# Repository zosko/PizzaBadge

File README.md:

# Pizza Badge

8 Slices pizza badge presented with LEDs. Slices will light when they receive response from server how many points you have.

## Scheme

## Boards
Board|PCB Empty|PCB filled
---------|---------|---------
||

## 3D Case
With PCB|Case Empty
---------|---------
|

## PCB Design

For PCB design i will use services from SeeedFusion. 

Seeed Fusion PCB Assembly Service offers one-stop prototyping for PCB manufacture, PCB assembly and as a result they produce superior quality PCBs and Fast Turnkey PCBA from 7 working days. When you prototype with Seeed Fusion, they can definitely provide Free DFA and Free functional tests for you! 

Check out their website to know about their manufacturing capabilities and service.
https://www.seeedstudio.com/prototype-pcb-assembly.html 

## Seeed Fusion PCBs
Empty PCB|Finished PCB
--------|--------
|

## Demo

## Reasons to choose Seeed Studio
- They provide PCB services at extremely low pricing and with excellent quality.
- Their offer is structured in such a way that everyone may have these boards at a reasonable price.
- They have a highly knowledgeable crew that leads their clients to avail deals and guides them about the costs and rates of different services.
- A four-layer board with a comparable feature costs $5 for 10 pieces and is made in four days.
- SMT stencil with size (10cm x 13cm) is available for $8.00 per piece.

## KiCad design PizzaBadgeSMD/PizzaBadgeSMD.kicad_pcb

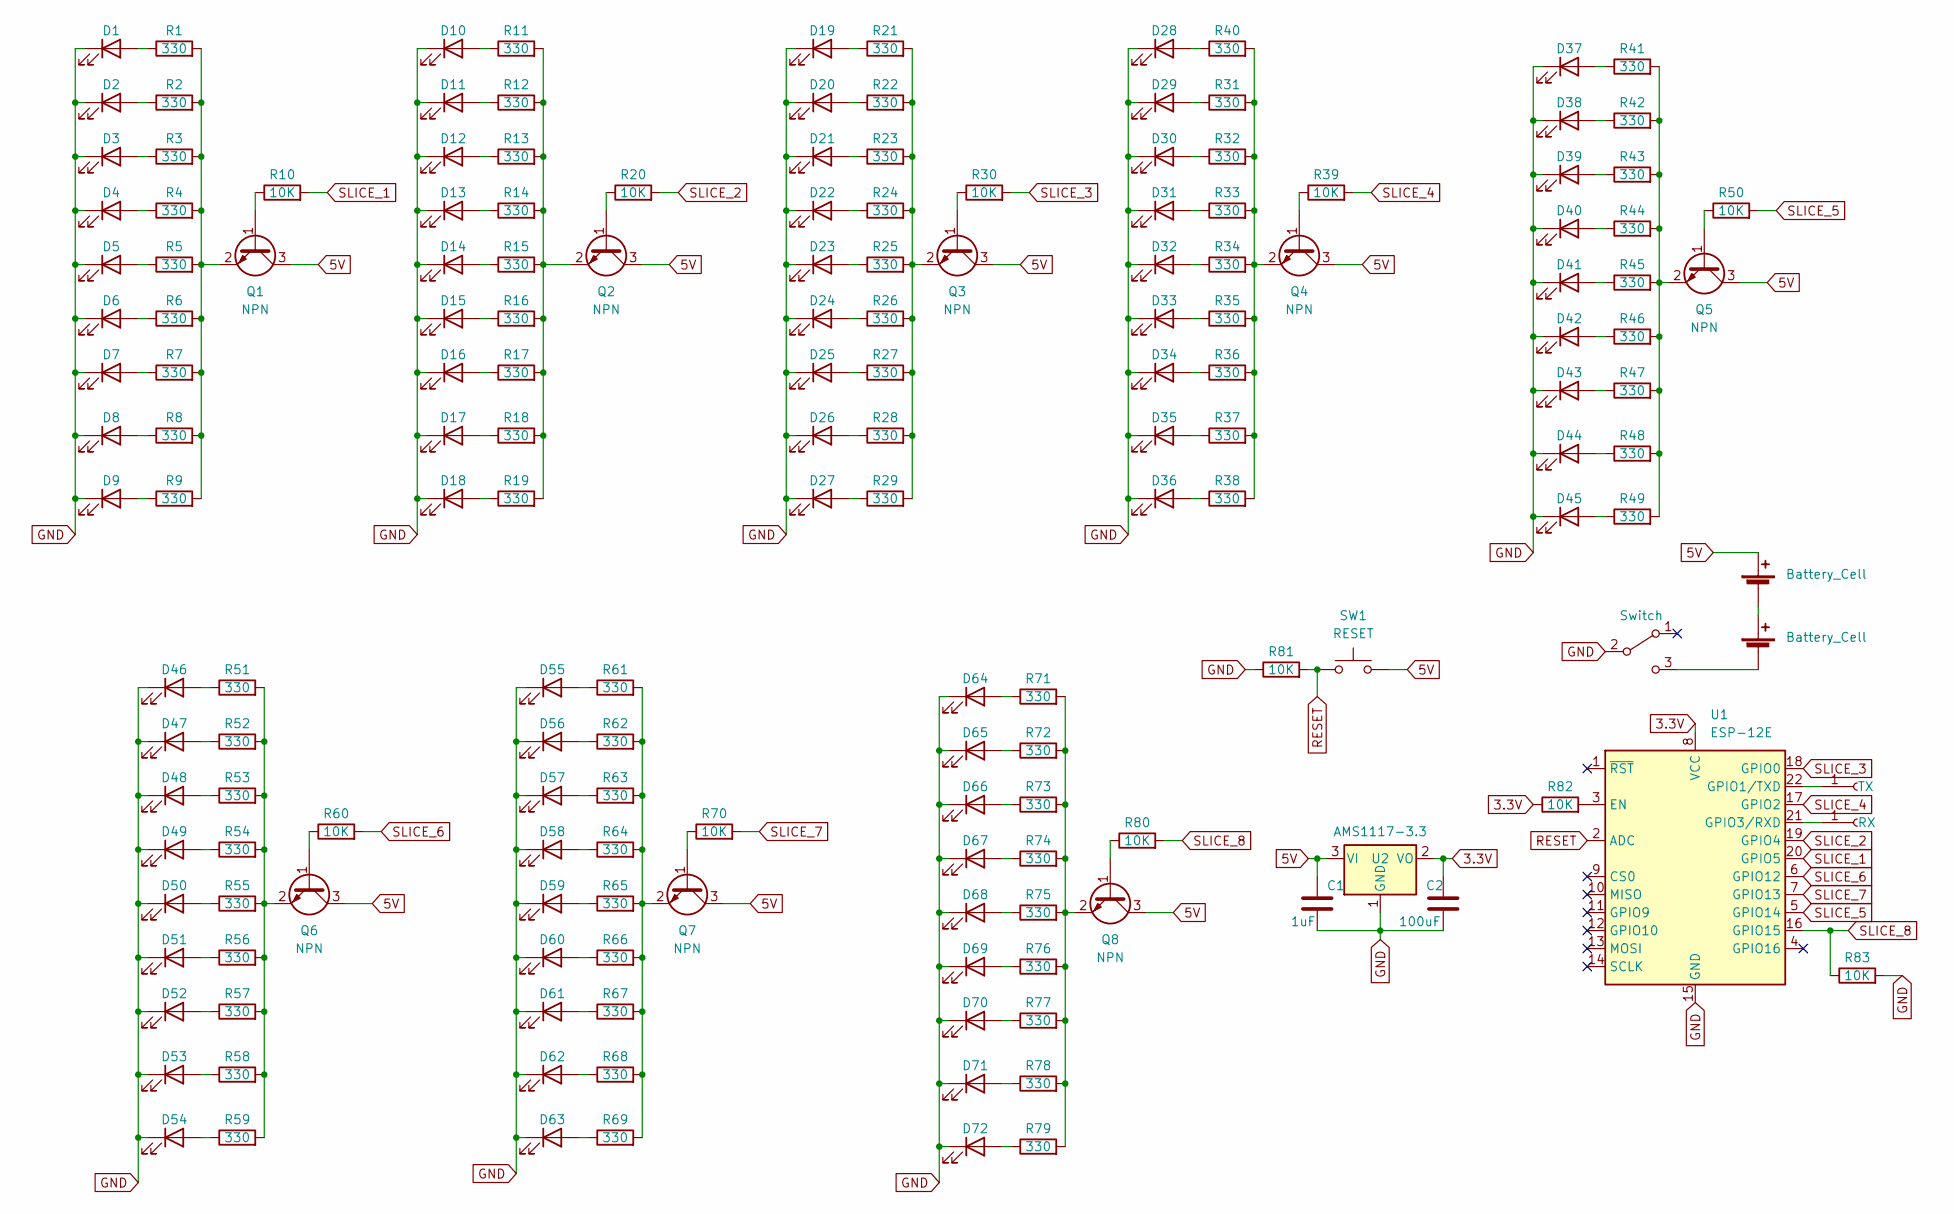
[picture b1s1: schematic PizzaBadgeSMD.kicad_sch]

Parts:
BT1, BT2: Battery_Cell; BatteryHolder_Keystone_3000_1x12mm
C1: 1uF; C_0805_2012Metric
C2: 100uF; C_0805_2012Metric
D1, D2, D3, D4, D5, D6, D7, D8, D9, D10, D11, D12, D13, D14, D15, D16, D17, D18, D19, D20, D21, D22, D23, D24, D25, D26, D27, D28, D29, D30, D31, D32, D33, D34, D35, D36, D37, D38, D39, D40, D41, D42, D43, D44, D45, D46, D47, D48, D49, D50, D51, D52, D53, D54, D55, D56, D57, D58, D59, D60, D61, D62, D63, D64, D65, D66, D67, D68, D69, D70, D71, D72: LED; LED_0805_2012Metric
J1: TX; TestPoint_Pad_2.0x2.0mm
J2: RX; TestPoint_Pad_2.0x2.0mm
Q1, Q2, Q3, Q4, Q5, Q6, Q7, Q8: NPN; SOT-23
R1, R2, R3, R4, R5, R6, R7, R8, R9, R11, R12, R13, R14, R15, R16, R17, R18, R19, R21, R22, R23, R24, R25, R26, R27, R28, R29, R31, R32, R33, R34, R35, R36, R37, R38, R40, R41, R42, R43, R44, R45, R46, R47, R48, R49, R51, R52, R53, R54, R55, R56, R57, R58, R59, R61, R62, R63, R64, R65, R66, R67, R68, R69, R71, R72, R73, R74, R75, R76, R77, R78, R79: 330; R_0805_2012Metric
R10, R20, R30, R39, R50, R60, R70, R80, R81, R82, R83: 10K; R_0805_2012Metric
SW1: RESET; SW_SPST_CK_RS282G05A3
SW2: Switch; SW_SPDT_PCM12
U1: ESP-12E
U2: AMS1117-3.3; SOT-223-3_TabPin2

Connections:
3.3V: C2.1, R82.1, U1.8 (VCC), U2.2 (VO)
5V: BT1.1 (+), C1.1, Q1.3 (C), Q2.3 (C), Q3.3 (C), Q4.3 (C), Q5.3 (C), Q6.3 (C), Q7.3 (C), Q8.3 (C), SW1.2, U2.3 (VI)
GND: C1.2, C2.2, D1.1 (K), D2.1 (K), D3.1 (K), D4.1 (K), D5.1 (K), D6.1 (K), D7.1 (K), D8.1 (K), D9.1 (K), D10.1 (K), D11.1 (K), D12.1 (K), D13.1 (K), D14.1 (K), D15.1 (K), D16.1 (K), D17.1 (K), D18.1 (K), D19.1 (K), D20.1 (K), D21.1 (K), D22.1 (K), D23.1 (K), D24.1 (K), D25.1 (K), D26.1 (K), D27.1 (K), D28.1 (K), D29.1 (K), D30.1 (K), D31.1 (K), D32.1 (K), D33.1 (K), D34.1 (K), D35.1 (K), D36.1 (K), D37.1 (K), D38.1 (K), D39.1 (K), D40.1 (K), D41.1 (K), D42.1 (K), D43.1 (K), D44.1 (K), D45.1 (K), D46.1 (K), D47.1 (K), D48.1 (K), D49.1 (K), D50.1 (K), D51.1 (K), D52.1 (K), D53.1 (K), D54.1 (K), D55.1 (K), D56.1 (K), D57.1 (K), D58.1 (K), D59.1 (K), D60.1 (K), D61.1 (K), D62.1 (K), D63.1 (K), D64.1 (K), D65.1 (K), D66.1 (K), D67.1 (K), D68.1 (K), D69.1 (K), D70.1 (K), D71.1 (K), D72.1 (K), R81.1, R83.2, SW2.2 (B), U1.15 (GND), U2.1 (GND)
unnamed: BT1.2 (-), BT2.1 (+)
unnamed: BT2.2 (-), SW2.3 (C)
unnamed: D1.2 (A), R1.1
unnamed: D2.2 (A), R2.1
unnamed: D3.2 (A), R3.1
unnamed: D4.2 (A), R4.1
unnamed: D5.2 (A), R5.1
unnamed: D6.2 (A), R6.1
unnamed: D7.2 (A), R7.1
unnamed: D8.2 (A), R8.1
unnamed: D9.2 (A), R9.1
unnamed: D10.2 (A), R11.1
unnamed: D11.2 (A), R12.1
unnamed: D12.2 (A), R13.1
unnamed: D13.2 (A), R14.1
unnamed: D14.2 (A), R15.1
unnamed: D15.2 (A), R16.1
unnamed: D16.2 (A), R17.1
unnamed: D17.2 (A), R18.1
unnamed: D18.2 (A), R19.1
unnamed: D19.2 (A), R21.1
unnamed: D20.2 (A), R22.1
unnamed: D21.2 (A), R23.1
unnamed: D22.2 (A), R24.1
unnamed: D23.2 (A), R25.1
unnamed: D24.2 (A), R26.1
unnamed: D25.2 (A), R27.1
unnamed: D26.2 (A), R28.1
unnamed: D27.2 (A), R29.1
unnamed: D28.2 (A), R40.1
unnamed: D29.2 (A), R31.1
unnamed: D30.2 (A), R32.1
unnamed: D31.2 (A), R33.1
unnamed: D32.2 (A), R34.1
unnamed: D33.2 (A), R35.1
unnamed: D34.2 (A), R36.1
unnamed: D35.2 (A), R37.1
unnamed: D36.2 (A), R38.1
unnamed: D37.2 (A), R41.1
unnamed: D38.2 (A), R42.1
unnamed: D39.2 (A), R43.1
unnamed: D40.2 (A), R44.1
unnamed: D41.2 (A), R45.1
unnamed: D42.2 (A), R46.1
unnamed: D43.2 (A), R47.1
unnamed: D44.2 (A), R48.1
unnamed: D45.2 (A), R49.1
unnamed: D46.2 (A), R51.1
unnamed: D47.2 (A), R52.1
unnamed: D48.2 (A), R53.1
unnamed: D49.2 (A), R54.1
unnamed: D50.2 (A), R55.1
unnamed: D51.2 (A), R56.1
unnamed: D52.2 (A), R57.1
unnamed: D53.2 (A), R58.1
unnamed: D54.2 (A), R59.1
unnamed: D55.2 (A), R61.1
unnamed: D56.2 (A), R62.1
unnamed: D57.2 (A), R63.1
unnamed: D58.2 (A), R64.1
unnamed: D59.2 (A), R65.1
unnamed: D60.2 (A), R66.1
unnamed: D61.2 (A), R67.1
unnamed: D62.2 (A), R68.1
unnamed: D63.2 (A), R69.1
unnamed: D64.2 (A), R71.1
unnamed: D65.2 (A), R72.1
unnamed: D66.2 (A), R73.1
unnamed: D67.2 (A), R74.1
unnamed: D68.2 (A), R75.1
unnamed: D69.2 (A), R76.1
unnamed: D70.2 (A), R77.1
unnamed: D71.2 (A), R78.1
unnamed: D72.2 (A), R79.1
unnamed: Q1.1 (B), R10.1
unnamed: Q1.2 (E), R1.2, R2.2, R3.2, R4.2, R5.2, R6.2, R7.2, R8.2, R9.2
unnamed: Q2.1 (B), R20.1
unnamed: Q2.2 (E), R11.2, R12.2, R13.2, R14.2, R15.2, R16.2, R17.2, R18.2, R19.2
unnamed: Q3.1 (B), R30.1
unnamed: Q3.2 (E), R21.2, R22.2, R23.2, R24.2, R25.2, R26.2, R27.2, R28.2, R29.2
unnamed: Q4.1 (B), R39.1
unnamed: Q4.2 (E), R31.2, R32.2, R33.2, R34.2, R35.2, R36.2, R37.2, R38.2, R40.2
unnamed: Q5.1 (B), R50.1
unnamed: Q5.2 (E), R41.2, R42.2, R43.2, R44.2, R45.2, R46.2, R47.2, R48.2, R49.2
unnamed: Q6.1 (B), R60.1
unnamed: Q6.2 (E), R51.2, R52.2, R53.2, R54.2, R55.2, R56.2, R57.2, R58.2, R59.2
unnamed: Q7.1 (B), R70.1
unnamed: Q7.2 (E), R61.2, R62.2, R63.2, R64.2, R65.2, R66.2, R67.2, R68.2, R69.2
unnamed: Q8.1 (B), R80.1
unnamed: Q8.2 (E), R71.2, R72.2, R73.2, R74.2, R75.2, R76.2, R77.2, R78.2, R79.2
unnamed: R82.2, U1.3 (EN)
unnamed: J2.1, U1.21 (GPIO3/RXD)
unnamed: J1.1, U1.22 (GPIO1/TXD)
RESET: R81.2, SW1.1, U1.2 (ADC)
SLICE_1: R10.2, U1.20 (GPIO5)
SLICE_2: R20.2, U1.19 (GPIO4)
SLICE_3: R30.2, U1.18 (GPIO0)
SLICE_4: R39.2, U1.17 (GPIO2)
SLICE_5: R50.2, U1.5 (GPIO14)
SLICE_6: R60.2, U1.6 (GPIO12)
SLICE_7: R70.2, U1.7 (GPIO13)
SLICE_8: R80.2, R83.1, U1.16 (GPIO15)

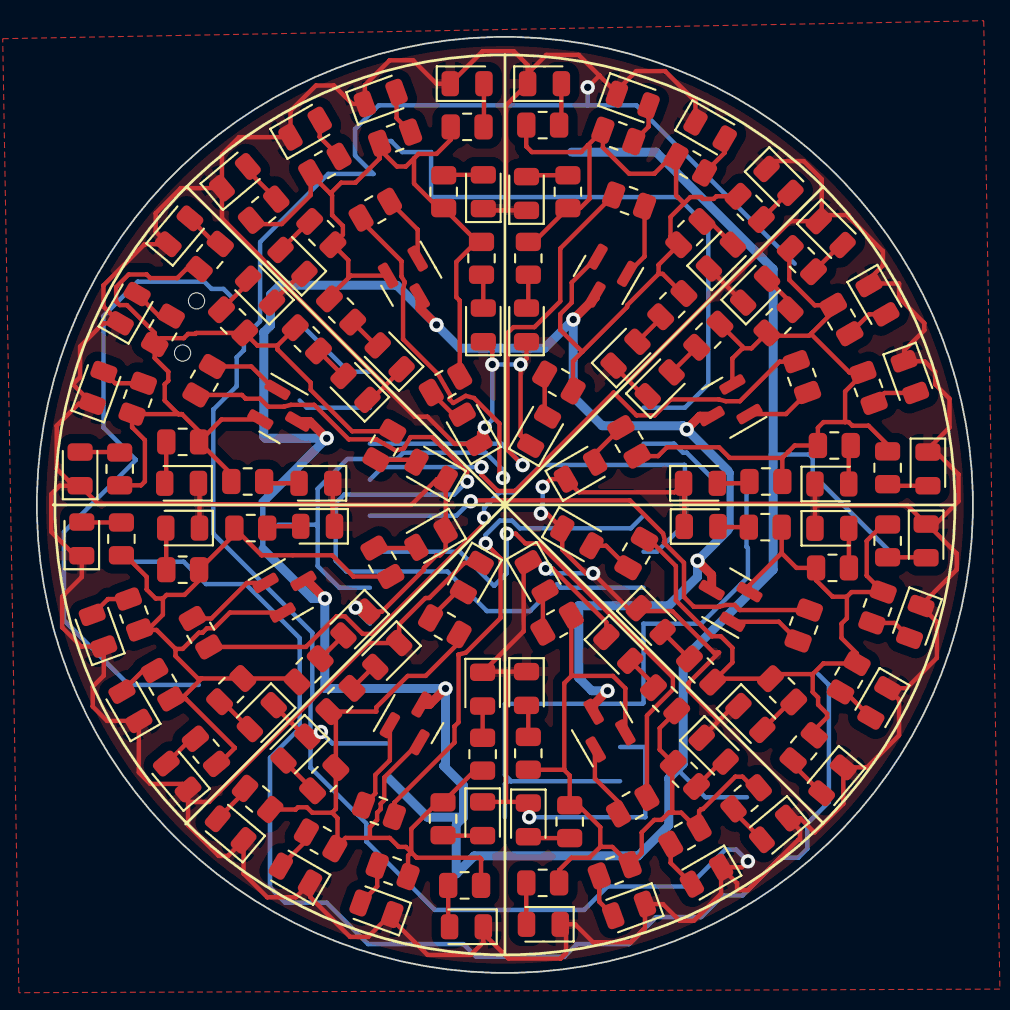
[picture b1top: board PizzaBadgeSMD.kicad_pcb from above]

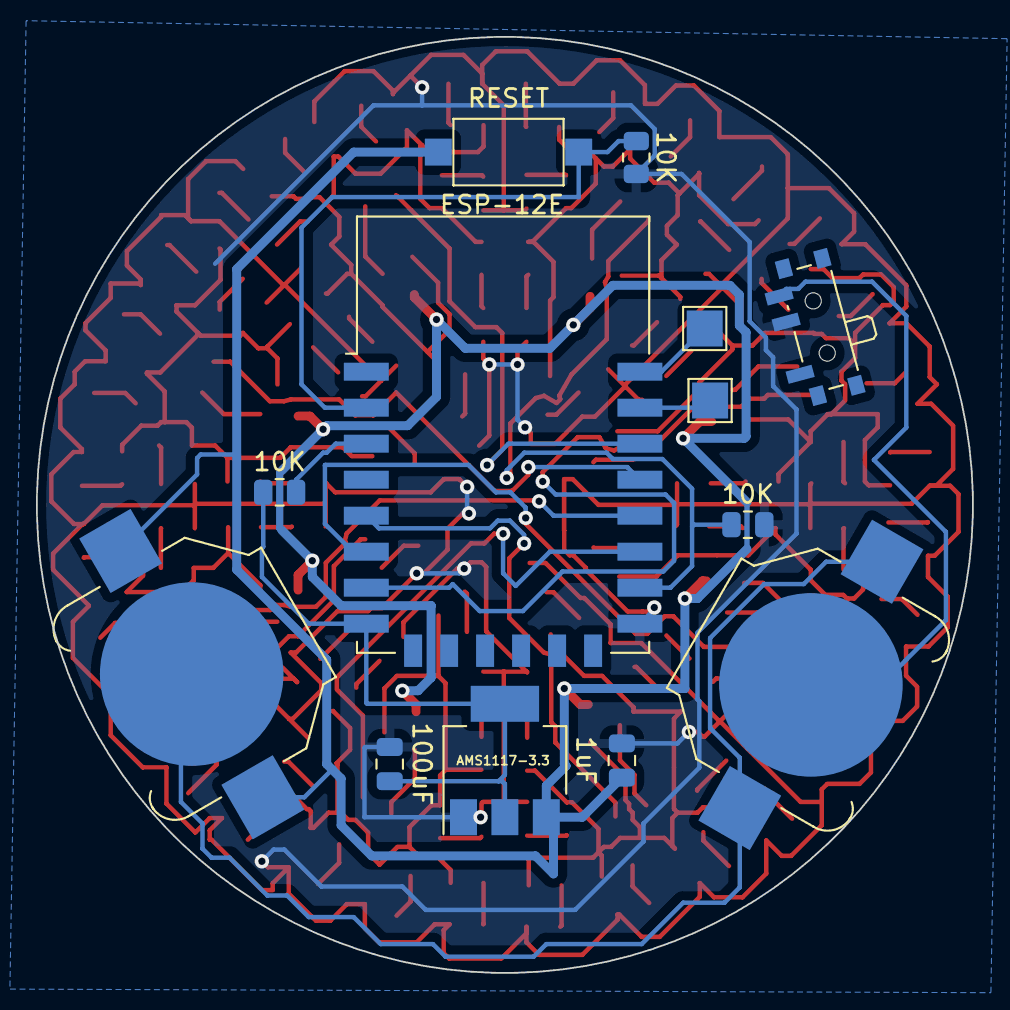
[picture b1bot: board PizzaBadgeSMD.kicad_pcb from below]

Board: 2 copper layers, 52.0 x 52.0 mm, 173 parts (13 on the bottom side), 105 nets.

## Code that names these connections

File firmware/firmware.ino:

#include <WiFiManager.h>
#include <EEPROM.h>
#include <ESP8266HTTPClient.h>

const int pin_reset = A0;
const int pin_slice_1 = D1;
const int pin_slice_2 = D2;
const int pin_slice_3 = D3;
const int pin_slice_4 = D4;
const int pin_slice_5 = D5;
const int pin_slice_6 = D6;
const int pin_slice_7 = D7;
const int pin_slice_8 = D8;

const int allPins[8] = { pin_slice_1, pin_slice_2, pin_slice_3, pin_slice_4,
                         pin_slice_5, pin_slice_6, pin_slice_7, pin_slice_8
                       };

WiFiManager wm;
WiFiManagerParameter custom_field;
bool shouldSaveConfig = false;
String webURLParam = "";

void setup() {
  Serial.begin(115200);
  EEPROM.begin(512);
  WiFi.mode(WIFI_STA);

  for (int i = 0; i < 8; i++) {
    pinMode(allPins[i], OUTPUT);
  }
  turnOffAll();

  wm.setTitle("Pizza Badge");

  const char* custom_server_str = "<br/><label for='customfieldid'>Enter Email</label><input type='text' name='customfieldid'>";
  new (&custom_field) WiFiManagerParameter(custom_server_str);
  wm.addParameter(&custom_field);
  wm.setSaveParamsCallback(saveParamCallback);

  std::vector<const char *> wm_menu  = {"wifi"};
  wm.setShowInfoUpdate(false);
  wm.setShowInfoErase(false);
  wm.setMenu(wm_menu);

  bool res;
  res = wm.autoConnect("PizzaBadgeAP");

  if (!res) {
    Serial.println("Failed to connect");
  }
  else {
    Serial.println("connected...yeey :)");
    if (shouldSaveConfig) {
      writeCodeToEEPROM(webURLParam);
      delay(100);
    }
    webURLParam = readCodeFromEEPROM();
    delay(100);
    Serial.print("LOADED FROM EEPROM:[");
    Serial.print(webURLParam);
    Serial.println("]");
  }

  pinMode(pin_reset, INPUT_PULLUP);
}

void loop() {
  checkForPizzaPoint();
  delay(5000);

  // SMD version > 1000
  // Normal version < 1000
  if (analogRead(pin_reset) > 1000) { 
    animateReset();
    factoryReset();
  }
}

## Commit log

2022-04-05 fix scheme, fix board, add reset button, revision1
2022-04-06 update images
2022-04-06 new scheme
2022-04-06 add reset button
2022-04-06 tidy server
2022-04-07 add new images
2022-04-07 added case
2022-04-07 separate firmware
2022-04-11 silk improve
2022-04-14 meta filename
2022-04-30 led animation
2022-04-30 smd version
2022-04-30 new images
2022-04-30 resize
2022-05-09 update code
2022-05-09 remove old 3d case
2022-05-09 new 3d printable case
2022-05-10 update server
2022-05-10 add frontend
2022-05-30 fill board
2022-05-31 captive screen improve, add new animation
2022-05-31 improvments, add new state
2022-06-30 update SMD version
2022-07-08 add coin battery
2022-07-08 improve traces
2022-07-08 change switch button
2022-07-14 update scheme and board on smd
2022-07-14 remove smd project
